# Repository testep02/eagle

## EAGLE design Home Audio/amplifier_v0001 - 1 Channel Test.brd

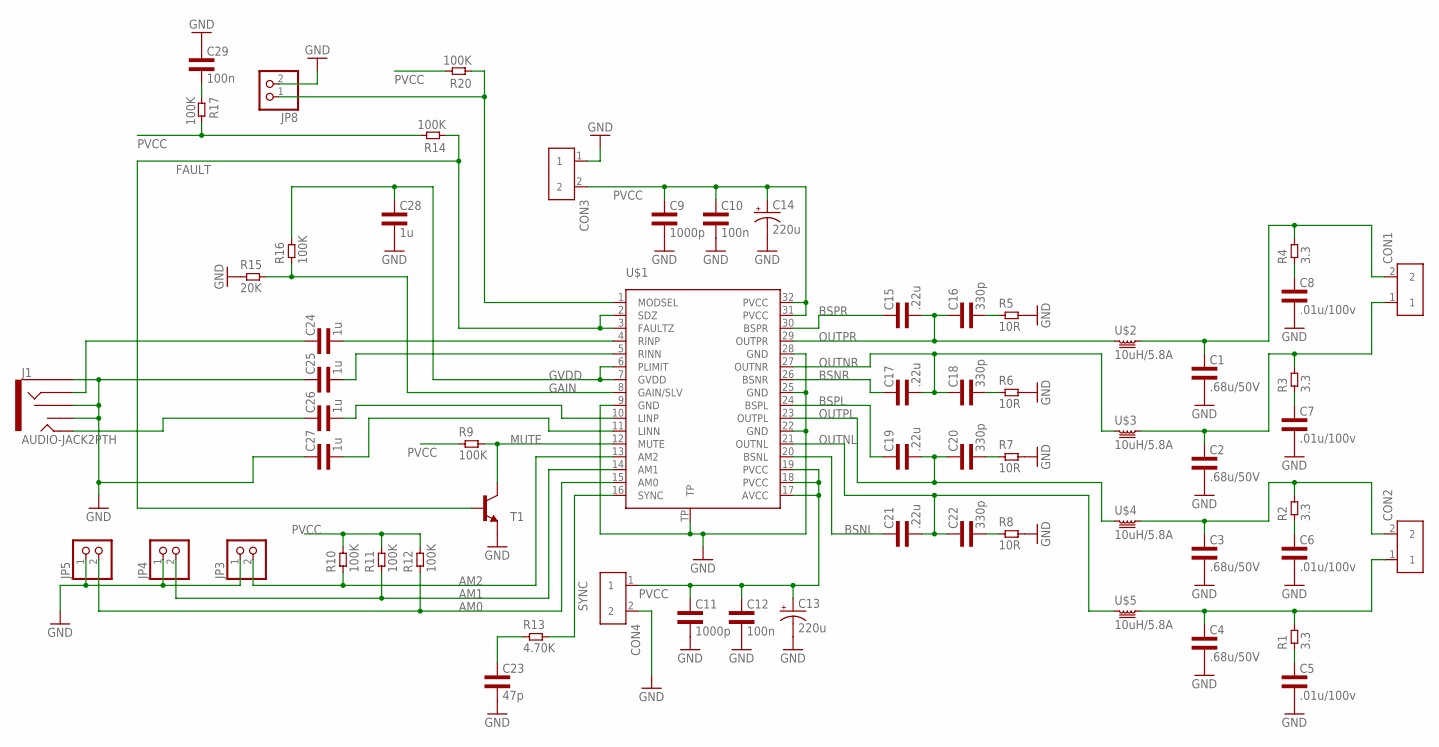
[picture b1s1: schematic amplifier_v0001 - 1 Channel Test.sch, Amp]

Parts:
C1, C2, C3, C4: .68u/50V; 1206L3
C5, C6, C7, C8: .01u/100v; 0805L3
C9, C11: 1000p; 0603L3
C10, C12, C29: 100n; 0603L3
C13, C14: 220u; E5-10,5
C15, C17, C19, C21: .22u; 0603L3
C16, C18, C20, C22: 330p; 0603L3
C23: 47p; 0603L3
C24, C25, C26, C27, C28: 1u; 0603L3
CON1, CON2, CON3, CON4: TERM_BLOCK_2
J1: AUDIO-JACK2PTH; AUDIO-JACK
JP3, JP4, JP5, JP8: PINHD-1X2; 1X02
R1, R2, R3, R4: 3.3; 0603L3
R5, R6, R7, R8: 10R; 0805L3
R9, R10, R11, R12, R14, R16, R17, R20: 100K; 0603L3
R13: 4.70K; 0603L3
R15: 20K; 0603L3
T1: TRANSISTOR_MMBT2222ALT1-NPN-SOT23-BEC; TRANSISTOR_SOT23-BEC
U$1: TPA3116; R-PDSO-32
U$2, U$3, U$4, U$5: 10uH/5.8A; DR127

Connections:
AM0: JP5.2, R12.P$1 (1), U$1.15 (AM0)
AM1: JP4.2, R11.P$1 (1), U$1.14 (AM1)
AM2: JP3.2, R10.P$1 (1), U$1.13 (AM2)
BSNL: C21.P$1 (1), U$1.20 (BSNL)
BSNR: C17.P$1 (1), U$1.26 (BSNR)
BSPL: C19.P$1 (1), U$1.24 (BSPL)
BSPR: C15.P$1 (1), U$1.30 (BSPR)
FAULT: R14.P$1 (1), T1.B, U$1.2 (SDZ), U$1.3 (FAULTZ)
GAIN: R15.P$2 (2), R16.P$1 (1), U$1.8 (GAIN/SLV)
GND: C1.2, C2.2, C3.2, C4.2, C5.2, C6.2, C7.2, C8.2, C9.P$2 (2), C10.P$2 (2), C11.P$2 (2), C12.P$2 (2), C13.-, C14.-, C23.P$2 (2), C25.P$1 (1), C27.P$1 (1), C28.P$2 (2), C29.P$1 (1), CON3.1, CON4.2, J1.RSH, J1.SLEEVE, J1.TSH, JP3.1, JP4.1, JP5.1, JP8.2, R5.2, R6.2, R7.2, R8.2, R15.P$1 (1), T1.E, U$1.9 (GND), U$1.22 (GND), U$1.25 (GND), U$1.28 (GND), U$1.TP
GVDD: C28.P$1 (1), R16.P$2 (2), U$1.6 (PLIMIT), U$1.7 (GVDD)
LEFT+: C3.1, CON2.2, R2.P$2 (2), U$4.2
LEFT-: C4.1, CON2.1, R1.P$2 (2), U$5.2
MUTE: R9.P$2 (2), T1.C, U$1.12 (MUTE)
unnamed: C27.P$2 (2), U$1.11 (LINN)
unnamed: C26.P$2 (2), U$1.10 (LINP)
unnamed: C24.P$2 (2), U$1.4 (RINP)
unnamed: JP8.1, R20.P$1 (1), U$1.1 (MODSEL)
unnamed: C16.P$2 (2), R5.1
unnamed: C25.P$2 (2), U$1.5 (RINN)
unnamed: C29.P$2 (2), R17.P$1 (1)
unnamed: C18.P$2 (2), R6.1
unnamed: C5.1, R1.P$1 (1)
unnamed: C6.1, R2.P$1 (1)
unnamed: C7.1, R3.P$1 (1)
unnamed: C8.1, R4.P$1 (1)
unnamed: C26.P$1 (1), J1.TIP
unnamed: C20.P$2 (2), R7.1
unnamed: C24.P$1 (1), J1.RING
unnamed: C22.P$2 (2), R8.1
unnamed: C23.P$1 (1), R13.P$1 (1)
OUTNL: C21.P$2 (2), C22.P$1 (1), U$1.21 (OUTNL), U$5.1
OUTNR: C17.P$2 (2), C18.P$1 (1), U$1.27 (OUTNR), U$3.1
OUTPL: C19.P$2 (2), C20.P$1 (1), U$1.23 (OUTPL), U$4.1
OUTPR: C15.P$2 (2), C16.P$1 (1), U$1.29 (OUTPR), U$2.1
PVCC: C9.P$1 (1), C10.P$1 (1), C11.P$1 (1), C12.P$1 (1), C13.+, C14.+, CON3.2, CON4.1, R9.P$1 (1), R10.P$2 (2), R11.P$2 (2), R12.P$2 (2), R14.P$2 (2), R17.P$2 (2), R20.P$2 (2), U$1.17 (AVCC), U$1.18 (PVCC), U$1.19 (PVCC), U$1.31 (PVCC), U$1.32 (PVCC)
RIGHT+: C1.1, CON1.2, R4.P$2 (2), U$2.2
RIGHT-: C2.1, CON1.1, R3.P$2 (2), U$3.2
SYNC: R13.P$2 (2), U$1.16 (SYNC)

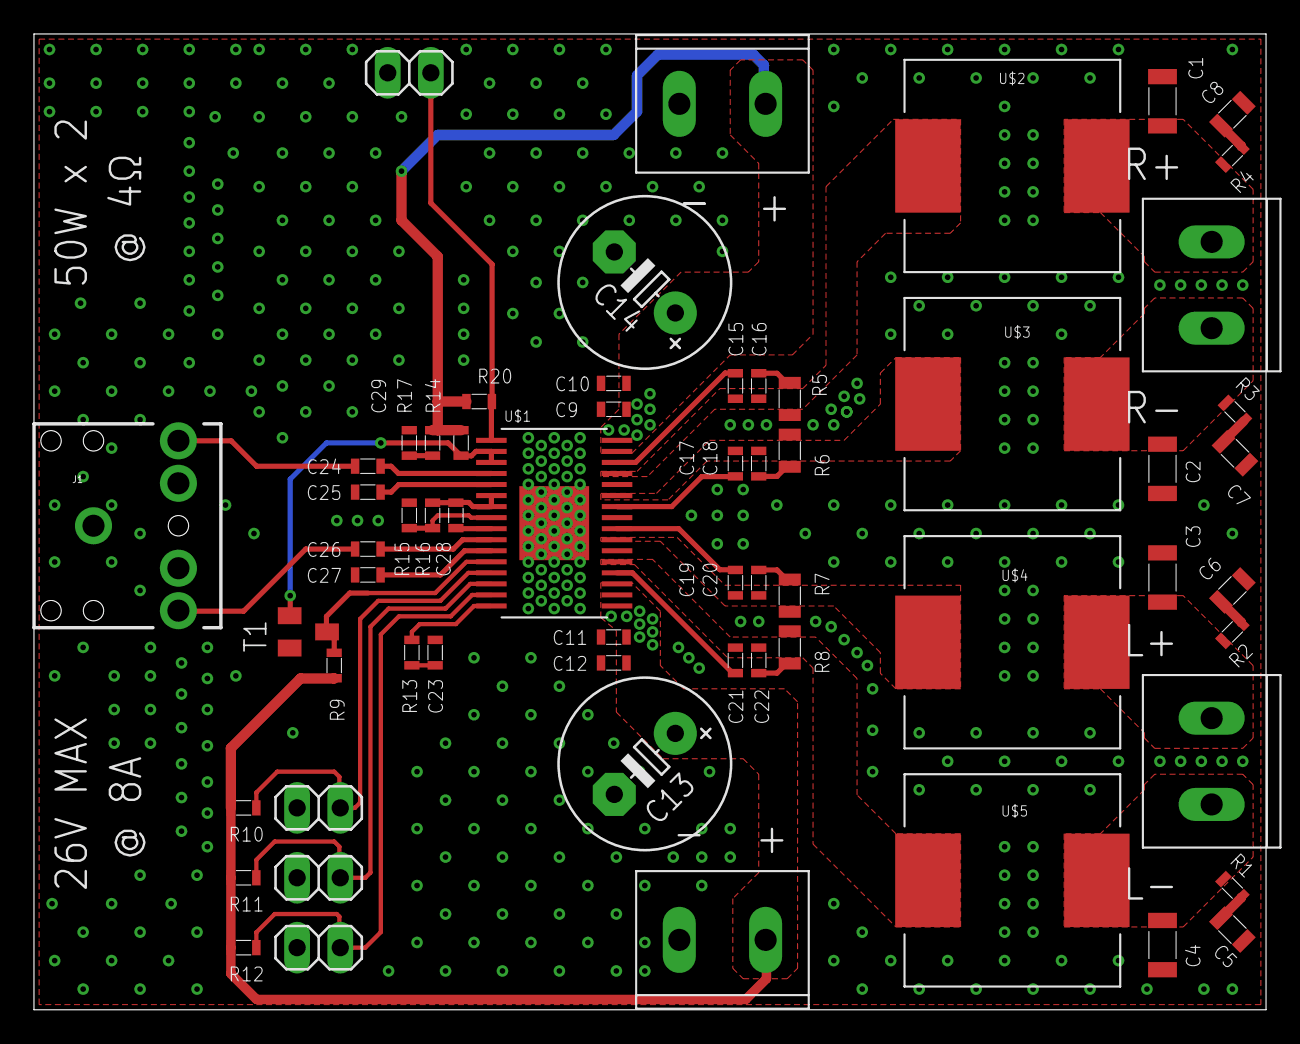
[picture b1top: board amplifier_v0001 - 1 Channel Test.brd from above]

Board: 2 copper layers, 72.5 x 57.5 mm, 62 parts (0 on the bottom side), 39 nets.

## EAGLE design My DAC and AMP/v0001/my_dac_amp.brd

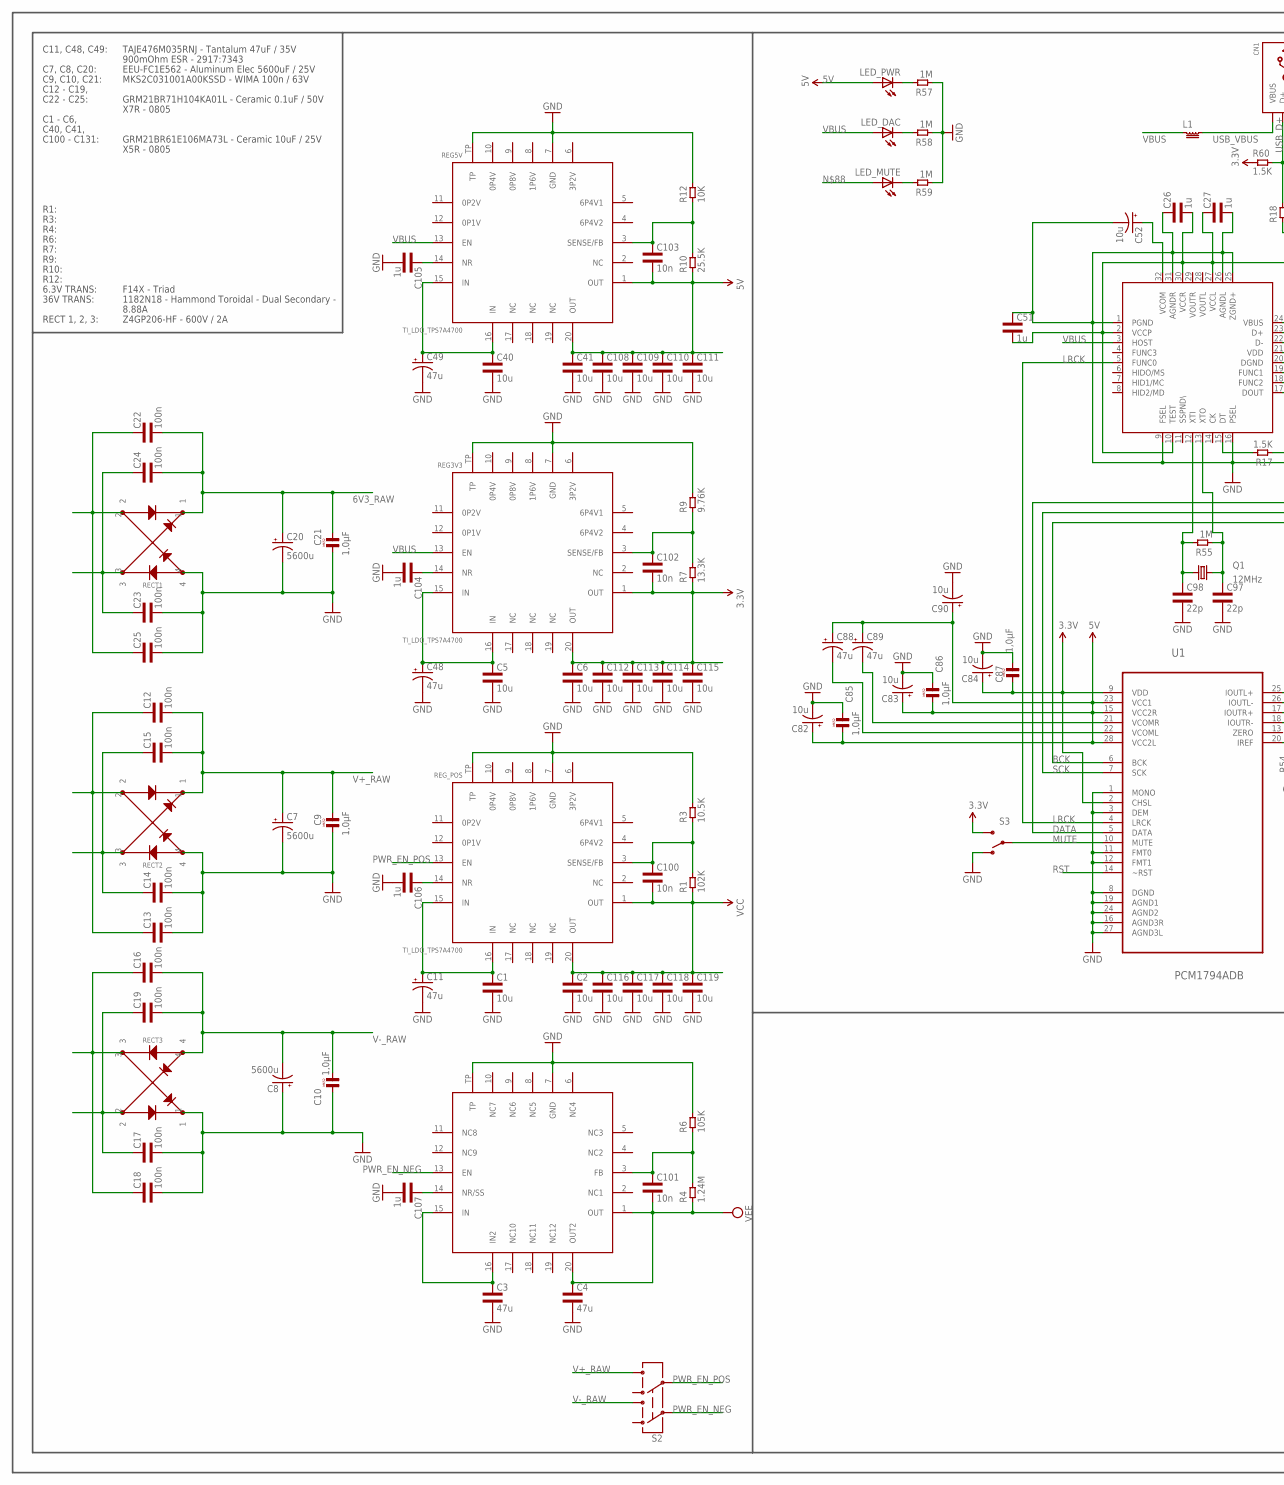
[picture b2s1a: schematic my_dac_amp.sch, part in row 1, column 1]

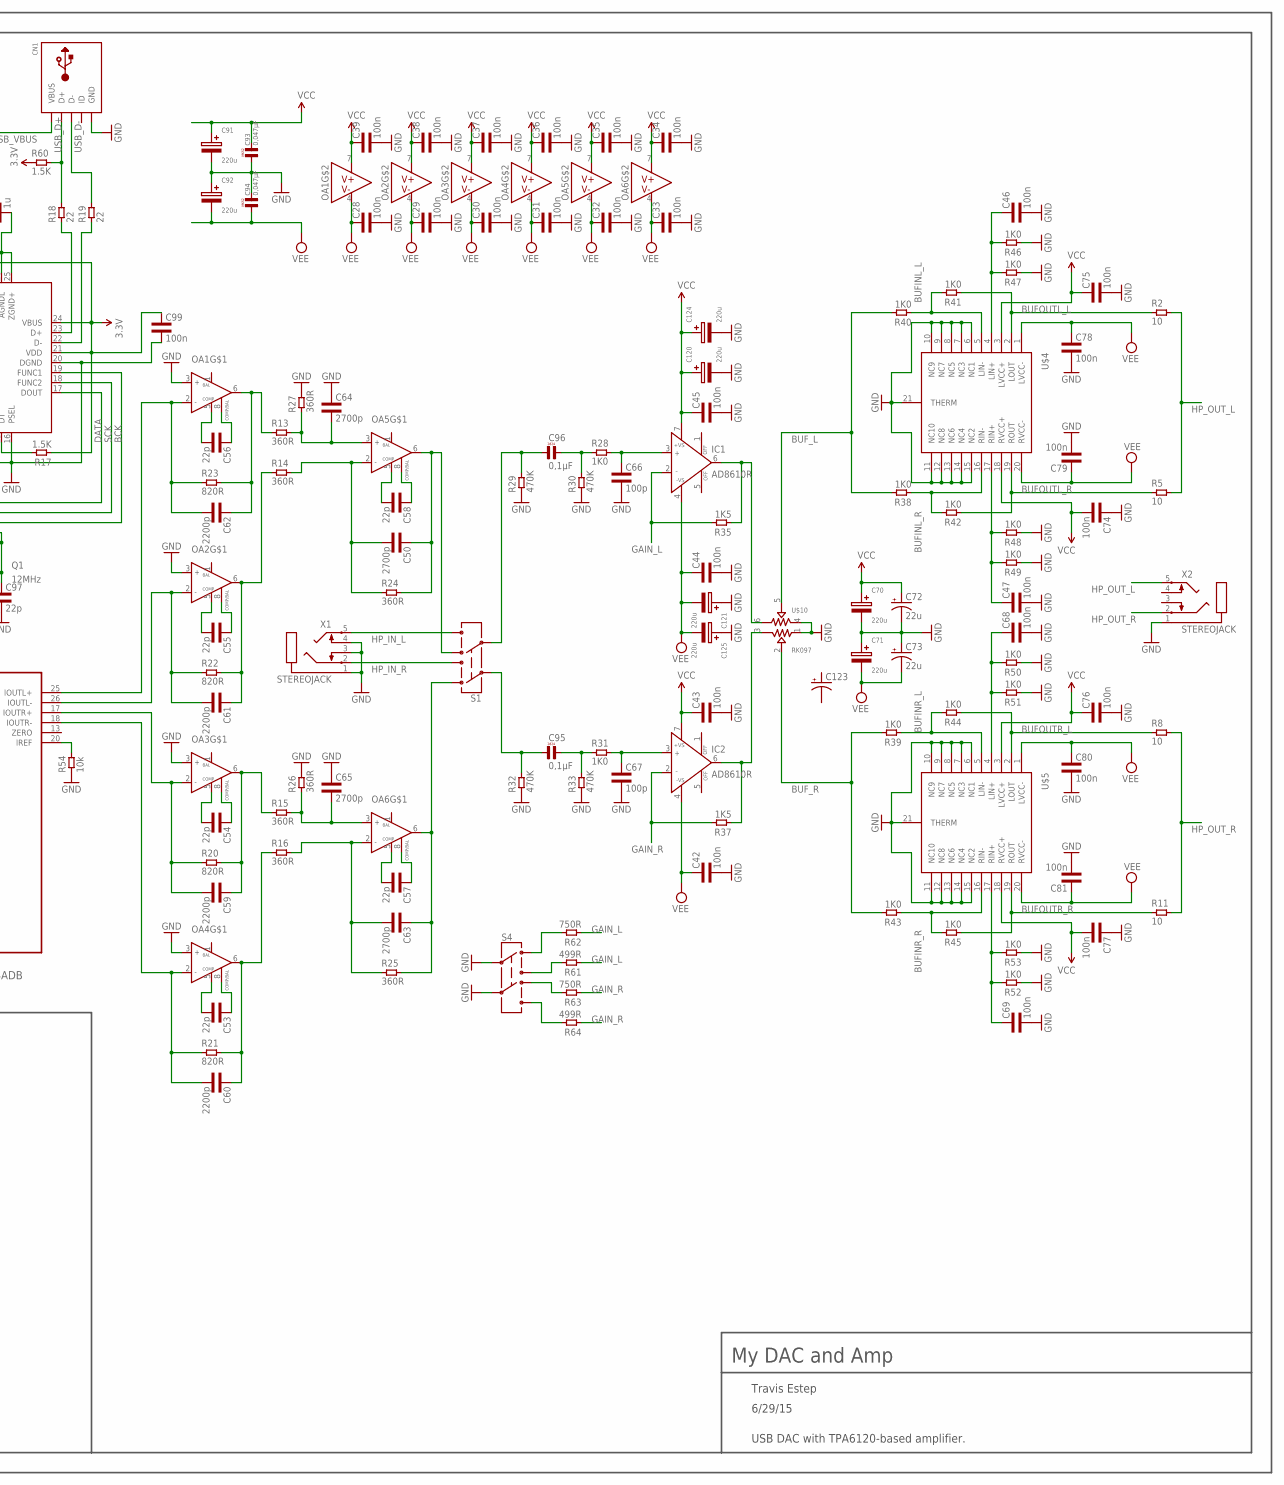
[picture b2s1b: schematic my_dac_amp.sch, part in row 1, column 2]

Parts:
C1, C5, C40: 10u; 1206L3
C2, C6, C41, C108, C109, C110, C111, C112, C113, C114, C115, C116, C117, C118, C119: 10u; 0805L3
C3, C4: 47u; 1206L3
C7, C8, C20: 5600u; E7,5-16
C9, C10, C21, C85, C86, C87: 1,0µF; R5B5
C11, C48, C49: 47u; SMC_E
C12, C13, C14, C15, C16, C17, C18, C19, C22, C23, C24, C25: 100n; 0805L3
C26, C27, C51, C104, C105, C106, C107: 1u; 0603L3
C28, C29, C30, C31, C32, C33, C34, C35, C36, C37, C38, C39, C42, C43, C44, C45, C46, C47, C68, C69, C74, C75, C76, C77, C78, C79, C80, C81, C99: 100n; 0603L3
C50, C63, C64, C65: 2700p; 0603L3
C52: 10u; E3,5-8
C53, C54, C55, C56, C57, C58, C97, C98: 22p; 0603L3
C59, C60, C61, C62: 2200p; 0603L3
C66, C67: 100p; 0603L3
C70, C71, C91, C92, C120, C121, C124, C125: 220u; 8066M
C72, C73: 22u; CT6032
C82, C83, C84, C90: 10u; A/3216-18W
C88, C89: 47u; B/3528-21R
C93, C94: 0,047µF; R5B2K5
C95, C96: 0,1µF; L7,2
C100, C101, C102, C103: 10n; 0603L3
C123: CPOL-USE/7260-38R; E/7260-38R
CN1: USBMINIB; USB-MINIB
IC1, IC2: AD8610R; SO8
L1: SRP4020; 4440
LED_DAC: LED3MM
LED_MUTE: LED3MM
LED_PWR: LED3MM
OA1, OA2, OA3, OA4, OA5, OA6: NE5534ADSOIC8; SOIC-8
Q1: 12MHz; SPARKFUN_HC49US
R1: 102K; 0603L3
R2, R5, R8, R11: 10; 1210L3
R3: 10.5K; 0603L3
R4: 1.24M; 0603L3
R6: 105K; 0603L3
R7: 13.3K; 0603L3
R9: 9.76K; 0603L3
R10: 25.5K; 0603L3
R12: 10K; 0603L3
R13, R14, R15, R16, R24, R25, R26, R27: 360R; 0603L3
R17, R60: 1.5K; 0603L3
R18, R19: 22; 0603L3
R20, R21, R22, R23: 820R; 0603L3
R28, R31, R38, R39, R40, R41, R42, R43, R44, R45, R46, R47, R48, R49, R50, R51, R52, R53: 1K0; 0603L3
R29, R30, R32, R33: 470K; 0603L3
R35, R37: 1K5; 0603L3
R54: 10k; 0603L3
R55, R57, R58, R59: 1M; 0603L3
R61, R64: 499R; 0603L3
R62, R63: 750R; 0603L3
RECT1, RECT2, RECT3: Z4GP206; ABS-4
REG3V3, REG5V: TI_LDO_TPS7A4700; TI_LDO_VQFN-20
REG_NEG: TI_LDO_TPS7A3301RGWT; TI_LDO_VQFN-20
REG_POS: TI_LDO_TPS7A4700; TI_LDO_VQFN-20
S1, S2, S4: SWITCH-DPDTOS; OS
S3: SWITCH-SPDTKIT; SWITCH-SPDT_KIT
U1: PCM1794ADB; SOP65P780X200-28N
U$3: PCM2704C_PCM2707
U$4, U$5: AMP_TPA6120_TPA6120
U$10: RK097
X1, X2: STEREOJACK; STX3100

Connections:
3.3V: C6.1, C26.P$2 (2), C27.P$1 (1), C51.P$2 (2), C84.+, C87.1, C99.P$1 (1), C102.P$2 (2), C112.1, C113.1, C114.1, C115.1, R7.P$1 (1), R17.P$1 (1), R60.P$1 (1), REG3V3.1 (OUT), REG3V3.20 (OUT), S3.3 (S), U1.2 (CHSL), U1.9 (VDD), U$3.2 (VCCP), U$3.10 (TEST), U$3.21 (VDD), U$3.24 (VBUS), U$3.27 (VCCL), U$3.30 (VCCR)
5V: C41.1, C82.+, C83.+, C85.1, C86.1, C88.+, C89.+, C90.+, C103.P$2 (2), C108.1, C109.1, C110.1, C111.1, LED_PWR.A, R10.P$1 (1), REG5V.1 (OUT), REG5V.20 (OUT), U1.15 (VCC2R), U1.23 (VCC1), U1.28 (VCC2L)
6V3_RAW: C5.1, C20.+, C21.2, C22.2, C24.2, C40.1, C48.+, C49.+, RECT1.1, REG3V3.15 (IN), REG3V3.16 (IN), REG5V.15 (IN), REG5V.16 (IN)
AMP_CAP_L: C96.P$2 (2), R28.P$1 (1), R30.P$2 (2)
AMP_CAP_R: C95.P$2 (2), R31.P$1 (1), R33.P$2 (2)
AMP_IN_L: C66.P$1 (1), IC1.3 (IN+), R28.P$2 (2)
AMP_IN_R: C67.P$1 (1), IC2.3 (IN+), R31.P$2 (2)
AMP_L: C96.P$1 (1), R29.P$2 (2), S1.5
AMP_OUT_L: IC1.6 (OUT), R35.P$1 (1), U$10.6
AMP_OUT_R: IC2.6 (OUT), R37.P$1 (1), U$10.3
AMP_R: C95.P$1 (1), R32.P$2 (2), S1.2
BCK: U1.6 (BCK), U$3.19 (FUNC1)
BUFINL_L: R40.P$1 (1), R41.P$2 (2), U$4.5 (LIN-)
BUFINL_R: R38.P$1 (1), R42.P$2 (2), U$4.16 (RIN-)
BUFINR_L: R39.P$1 (1), R44.P$2 (2), U$5.5 (LIN-)
BUFINR_R: R43.P$1 (1), R45.P$2 (2), U$5.16 (RIN-)
BUFL_L+: C46.P$1 (1), R46.P$2 (2), R47.P$2 (2), U$4.4 (LIN+)
BUFL_R+: C47.P$1 (1), R48.P$2 (2), R49.P$2 (2), U$4.17 (RIN+)
BUFOUTL_L: R2.P$1 (1), R41.P$1 (1), U$4.2 (LOUT)
BUFOUTL_R: R5.P$1 (1), R42.P$1 (1), U$4.19 (ROUT)
BUFOUTR_L: R8.P$1 (1), R44.P$1 (1), U$5.2 (LOUT)
BUFOUTR_R: R11.P$1 (1), R45.P$1 (1), U$5.19 (ROUT)
BUFR_L+: C68.P$1 (1), R50.P$2 (2), R51.P$2 (2), U$5.4 (LIN+)
BUFR_R+: C69.P$1 (1), R52.P$2 (2), R53.P$2 (2), U$5.17 (RIN+)
BUF_L: R38.P$2 (2), R40.P$2 (2), U$10.5
BUF_R: R39.P$2 (2), R43.P$2 (2), U$10.2
D+: R18.P$1 (1), U$3.23 (D+)
D-: R19.P$1 (1), U$3.22 (D-)
DATA: U1.5 (DATA), U$3.17 (DOUT)
GAINL_1: R62.P$2 (2), S4.1
GAINL_2: R61.P$2 (2), S4.3
GAINR_1: R63.P$2 (2), S4.4
GAINR_2: R64.P$2 (2), S4.6
GAIN_L: IC1.2 (IN-), R35.P$2 (2), R61.P$1 (1), R62.P$1 (1)
GAIN_R: IC2.2 (IN-), R37.P$2 (2), R63.P$1 (1), R64.P$1 (1)
GND: C1.2, C2.2, C3.2, C4.2, C5.2, C6.2, C7.-, C8.+, C9.1, C10.1, C11.-, C13.2, C14.2, C17.2, C18.2, C20.-, C21.1, C23.2, C25.2, C26.P$1 (1), C27.P$2 (2), C28.P$2 (2), C29.P$2 (2), C30.P$2 (2), C31.P$2 (2), C32.P$2 (2), C33.P$2 (2), C34.P$2 (2), C35.P$2 (2), C36.P$2 (2), C37.P$2 (2), C38.P$2 (2), C39.P$2 (2), C40.2, C41.2, C42.P$2 (2), C43.P$2 (2), C44.P$2 (2), C45.P$2 (2), C46.P$2 (2), C47.P$2 (2), C48.-, C49.-, C51.P$1 (1), C52.-, C64.P$1 (1), C65.P$1 (1), C66.P$2 (2), C67.P$2 (2), C68.P$2 (2), C69.P$2 (2), C70.2, C71.1, C72.-, C73.+, C74.P$1 (1), C75.P$2 (2), C76.P$2 (2), C77.P$1 (1), C78.P$2 (2), C79.P$2 (2), C80.P$2 (2), C81.P$2 (2), C82.-, C83.-, C84.-, C85.2, C86.2, C87.2, C90.-, C91.2, C92.1, C93.1, C94.2, C97.P$2 (2), C98.P$2 (2), C99.P$2 (2), C104.P$2 (2), C105.P$2 (2), C106.P$2 (2), C107.P$2 (2), C108.2, C109.2, C110.2, C111.2, C112.2, C113.2, C114.2, C115.2, C116.2, C117.2, C118.2, C119.2, C120.2, C121.1, C124.2, C125.1, CN1.GND, OA1.3 (IN+), OA2.3 (IN+), OA3.3 (IN+), OA4.3 (IN+), R3.P$2 (2), R6.P$2 (2), R9.P$2 (2), R12.P$2 (2), R26.P$2 (2), R27.P$2 (2), R29.P$1 (1), R30.P$1 (1), R32.P$1 (1), R33.P$1 (1), R46.P$1 (1), R47.P$1 (1), R48.P$1 (1), R49.P$1 (1), R50.P$1 (1), R51.P$1 (1), R52.P$1 (1), R53.P$1 (1), R54.P$1 (1), R57.P$1 (1), R58.P$1 (1), R59.P$1 (1), RECT1.4, RECT2.4, RECT3.1, REG3V3.7 (GND), REG3V3.TP, REG5V.7 (GND), REG5V.TP, REG_NEG.7 (GND), REG_NEG.TP, REG_POS.7 (GND), REG_POS.TP, S3.1 (O), S4.2, S4.5, U1.1 (MONO), U1.3 (DEM), U1.8 (DGND), U1.11 (FMT0), U1.12 (FMT1), U1.16 (AGND3R), U1.19 (AGND1), U1.24 (AGND2), U1.27 (AGND3L), U$3.1 (PGND), U$3.9 (FSEL), U$3.16 (PSEL), U$3.20 (DGND), U$3.25 (ZGND+), U$3.26 (AGNDL), U$3.31 (AGNDR), U$4.6 (NC1), U$4.7 (NC3), U$4.8 (NC5), U$4.9 (NC7), U$4.10 (NC9), U$4.11 (NC10), U$4.12 (NC8), U$4.13 (NC6), U$4.14 (NC4), U$4.15 (NC2), U$4.21 (THERM), U$5.6 (NC1), U$5.7 (NC3), U$5.8 (NC5), U$5.9 (NC7), U$5.10 (NC9), U$5.11 (NC10), U$5.12 (NC8), U$5.13 (NC6), U$5.14 (NC4), U$5.15 (NC2), U$5.21 (THERM), U$10.1, U$10.4, X1.1, X1.3, X1.4, X2.1
HP_IN_L: S1.6, X1.5
HP_IN_R: S1.3, X1.2
HP_OUT_L: R2.P$2 (2), R5.P$2 (2), X2.5
HP_OUT_R: R8.P$2 (2), R11.P$2 (2), X2.2
IOUTL+: C62.P$2 (2), OA1.2 (IN-), R23.P$1 (1), U1.25 (IOUTL+)
IOUTL-: C61.P$2 (2), OA2.2 (IN-), R22.P$1 (1), U1.26 (IOUTL-)
IOUTR+: C59.P$2 (2), OA3.2 (IN-), R20.P$1 (1), U1.17 (IOUTR+)
IOUTR-: C60.P$2 (2), OA4.2 (IN-), R21.P$1 (1), U1.18 (IOUTR-)
IVOUTR+: C59.P$1 (1), OA3.6 (OUT), R15.P$1 (1), R20.P$2 (2)
IVOUT_L-: C61.P$1 (1), OA2.6 (OUT), R14.P$1 (1), R22.P$2 (2)
IVOUT_R-: C60.P$1 (1), OA4.6 (OUT), R16.P$1 (1), R21.P$2 (2)
IVUOT_L+: C62.P$1 (1), OA1.6 (OUT), R13.P$1 (1), R23.P$2 (2)
LRCK: U1.4 (LRCK), U$3.5 (FUNC0)
MUTE: S3.2, U1.10 (MUTE)
unnamed: C103.P$1 (1), R10.P$2 (2), R12.P$1 (1), REG5V.3 (SENSE/FB)
unnamed: C100.P$1 (1), R1.P$2 (2), R3.P$1 (1), REG_POS.3 (SENSE/FB)
unnamed: LED_PWR.K (C), R57.P$2 (2)
unnamed: LED_DAC.K (C), R58.P$2 (2)
unnamed: C101.P$1 (1), R4.P$2 (2), R6.P$1 (1), REG_NEG.3 (FB)
unnamed: C12.1, C13.1, RECT2.2
unnamed: C14.1, C15.1, RECT2.3
unnamed: C102.P$1 (1), R7.P$2 (2), R9.P$1 (1), REG3V3.3 (SENSE/FB)
unnamed: C23.1, C24.1, RECT1.3
unnamed: C22.1, C25.1, RECT1.2
unnamed: C52.+, U$3.32 (VCOM)
unnamed: R17.P$2 (2), U$3.15 (DT)
unnamed: C107.P$1 (1), REG_NEG.14 (NR/SS)
unnamed: C106.P$1 (1), REG_POS.14 (NR)
unnamed: C104.P$1 (1), REG3V3.14 (NR)
unnamed: C105.P$1 (1), REG5V.14 (NR)
unnamed: C16.1, C18.1, RECT3.3
unnamed: C17.1, C19.1, RECT3.2
unnamed: C89.-, U1.21 (VCOMR)
unnamed: C88.-, U1.22 (VCOML)
unnamed: C98.P$1 (1), Q1.1, R55.P$2 (2), U$3.12 (XTI)
unnamed: C97.P$1 (1), Q1.2, R55.P$1 (1), U$3.13 (XTO)
unnamed: LED_MUTE.K (C), R59.P$2 (2)
unnamed: R54.P$2 (2), U1.20 (IREF)
OA1_COMP: C56.P$2 (2), OA1.5 (COMP)
OA1_COMPBAL: C56.P$1 (1), OA1.8 (COMP/BAL)
OA2_COMP: C55.P$2 (2), OA2.5 (COMP)
OA2_COMPBAL: C55.P$1 (1), OA2.8 (COMP/BAL)
OA3_COMP: C54.P$2 (2), OA3.5 (COMP)
OA3_COMPBAL: C54.P$1 (1), OA3.8 (COMP/BAL)
OA4_COMP: C53.P$2 (2), OA4.5 (COMP)
OA4_COMPBAL: C53.P$1 (1), OA4.8 (COMP/BAL)
OA5_COMP: C58.P$2 (2), OA5.5 (COMP)
OA5_COMPBAL: C58.P$1 (1), OA5.8 (COMP/BAL)
OA6_COMP: C57.P$2 (2), OA6.5 (COMP)
OA6_COMPBAL: C57.P$1 (1), OA6.8 (COMP/BAL)
PWR_EN_NEG: REG_NEG.13 (EN), S2.2
PWR_EN_POS: REG_POS.13 (EN), S2.5
RST: U1.14 (~RST)
SCK: U1.7 (SCK), U$3.18 (FUNC2)
SEIN_L+: C64.P$2 (2), OA5.3 (IN+), R13.P$2 (2), R27.P$1 (1)
SEIN_L-: C50.P$2 (2), OA5.2 (IN-), R14.P$2 (2), R24.P$1 (1)
SEIN_R+: C65.P$2 (2), OA6.3 (IN+), R15.P$2 (2), R26.P$1 (1)
SEIN_R-: C63.P$2 (2), OA6.2 (IN-), R16.P$2 (2), R25.P$1 (1)
SEOUT_L: C50.P$1 (1), OA5.6 (OUT), R24.P$2 (2), S1.4
SEOUT_R: C63.P$1 (1), OA6.6 (OUT), R25.P$2 (2), S1.1
USB_D+: CN1.D+, R18.P$2 (2), R60.P$2 (2)
USB_D-: CN1.D-, R19.P$2 (2)
USB_VBUS: CN1.VBUS, L1.2
V+_RAW: C1.1, C7.+, C9.2, C11.+, C12.2, C15.2, RECT2.1, REG_POS.15 (IN), REG_POS.16 (IN), S2.6
V-_RAW: C3.1, C8.-, C10.2, C16.2, C19.2, RECT3.4, REG_NEG.15 (IN), REG_NEG.16 (IN2), S2.3
VBUS: L1.1, LED_DAC.A, REG3V3.13 (EN), REG5V.13 (EN), U$3.3 (HOST)
VCC: C2.1, C34.P$1 (1), C35.P$1 (1), C36.P$1 (1), C37.P$1 (1), C38.P$1 (1), C39.P$1 (1), C43.P$1 (1), C45.P$1 (1), C70.1, C72.+, C74.P$2 (2), C75.P$1 (1), C76.P$1 (1), C77.P$2 (2), C91.1, C93.2, C100.P$2 (2), C116.1, C117.1, C118.1, C119.1, C120.1, C124.1, IC1.7 (+VS), IC2.7 (+VS), OA1.7 (V+), OA2.7 (V+), OA3.7 (V+), OA4.7 (V+), OA5.7 (V+), OA6.7 (V+), R1.P$1 (1), REG_POS.1 (OUT), REG_POS.20 (OUT), U$4.3 (LVCC+), U$4.18 (RVCC+), U$5.3 (LVCC+), U$5.18 (RVCC+)
VEE: C4.1, C28.P$1 (1), C29.P$1 (1), C30.P$1 (1), C31.P$1 (1), C32.P$1 (1), C33.P$1 (1), C42.P$1 (1), C44.P$1 (1), C71.2, C73.-, C78.P$1 (1), C79.P$1 (1), C80.P$1 (1), C81.P$1 (1), C92.2, C94.1, C101.P$2 (2), C121.2, C125.2, IC1.4 (-VS), IC2.4 (-VS), OA1.4 (V-), OA2.4 (V-), OA3.4 (V-), OA4.4 (V-), OA5.4 (V-), OA6.4 (V-), R4.P$1 (1), REG_NEG.1 (OUT), REG_NEG.20 (OUT2), U$4.1 (LVCC-), U$4.20 (RVCC-), U$5.1 (LVCC-), U$5.20 (RVCC-)

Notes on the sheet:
C11, C48, C49:
TAJE476M035RNJ - Tantalum 47uF / 35V
900mOhm ESR - 2917:7343
C7, C8, C20:
EEU-FC1E562 - Aluminum Elec 5600uF / 25V
RECT 1, 2, 3:
Z4GP206-HF - 600V / 2A
C9, C10, C21:
MKS2C031001A00KSSD - WIMA 100n / 63V
6.3V TRANS:
F14X - Triad
36V TRANS:
1182N18 - Hammond Toroidal - Dual Secondary -
8.88A
GRM21BR71H104KA01L - Ceramic 0.1uF / 50V
X7R - 0805
R1:
R3:
R4:
R6:
R7:
R9:
R10:
R12:
GRM21BR61E106MA73L - Ceramic 10uF / 25V
X5R - 0805
C12 - C19,
C22 - C25:
C1 - C6,
C40, C41,
C100 - C131:
My DAC and Amp
Travis Estep
6/29/15
USB DAC with TPA6120-based amplifier.

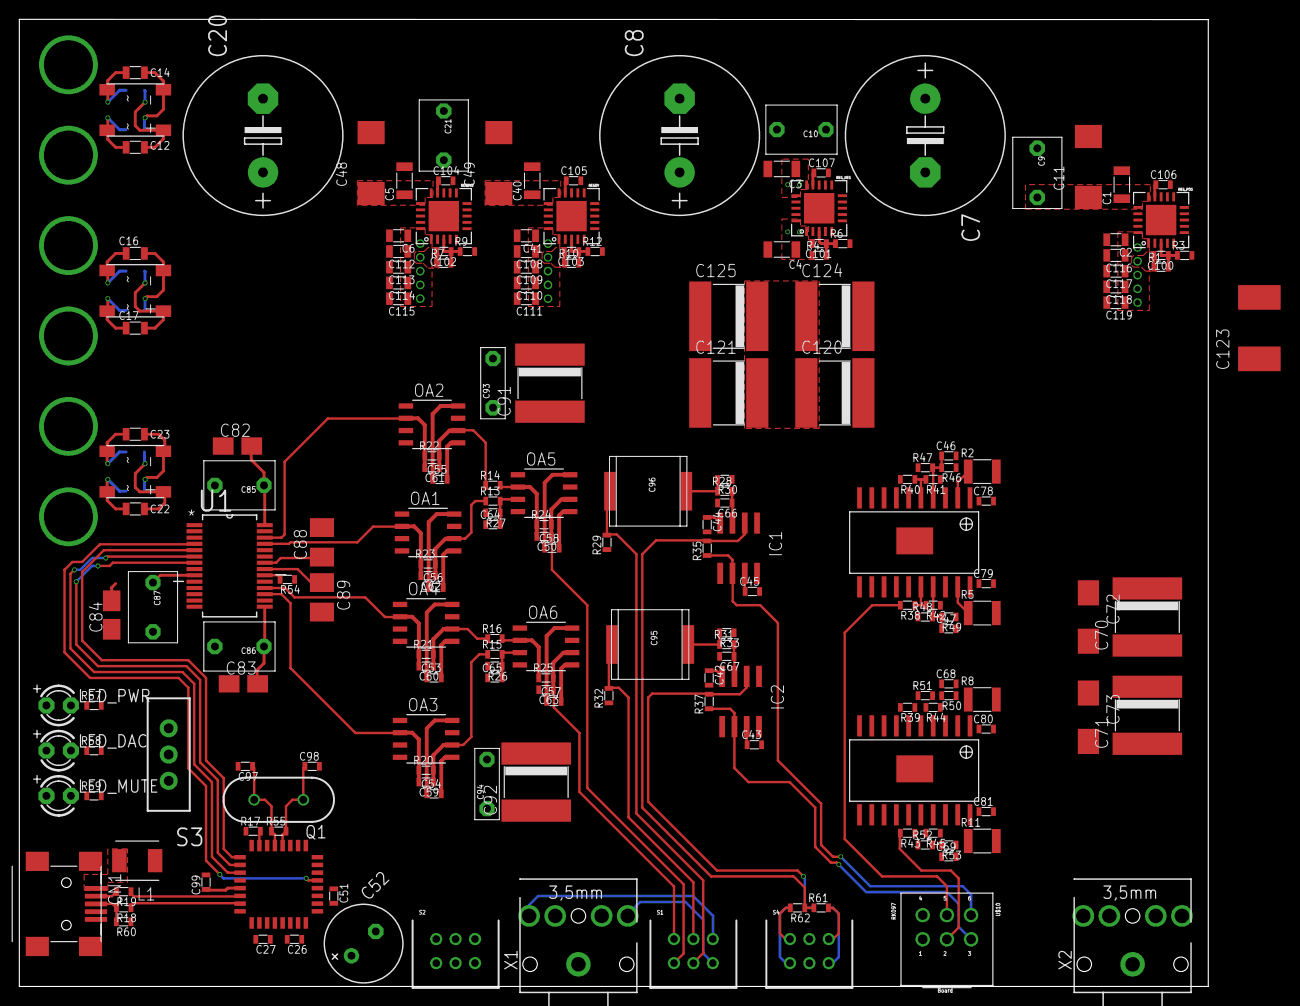
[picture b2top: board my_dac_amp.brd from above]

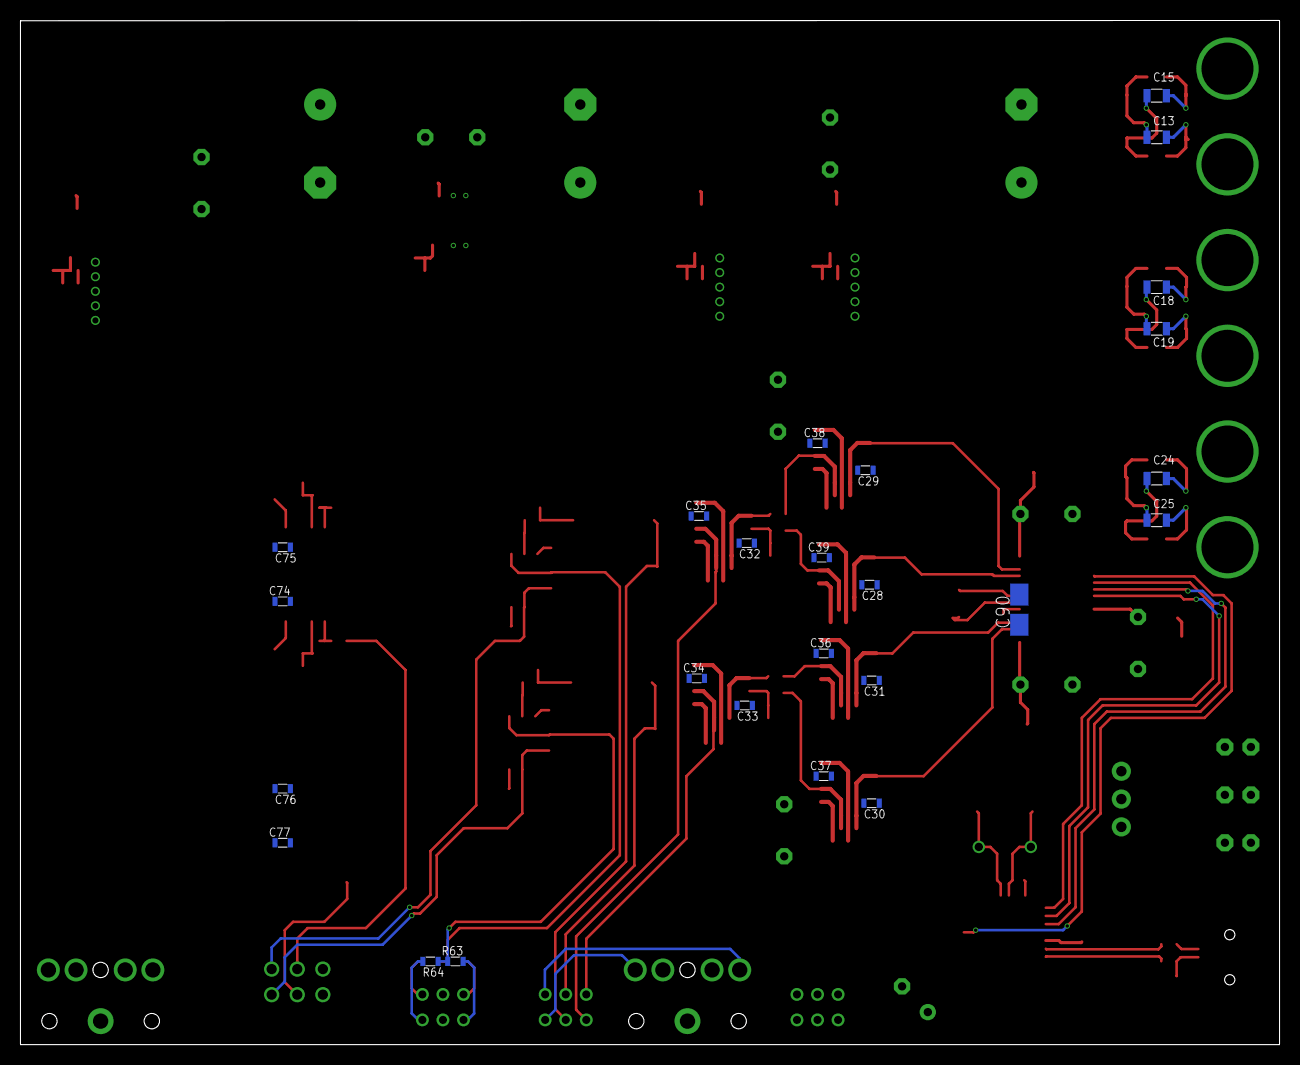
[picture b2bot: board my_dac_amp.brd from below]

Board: 4 copper layers, 122.9 x 100.0 mm, 217 parts (25 on the bottom side), 103 nets.

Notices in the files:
parts and their libraries:
SparkFun-Connectors: Licensing: CC v3.0 Share-Alike You are welcome to use this library for commercial purposes.
